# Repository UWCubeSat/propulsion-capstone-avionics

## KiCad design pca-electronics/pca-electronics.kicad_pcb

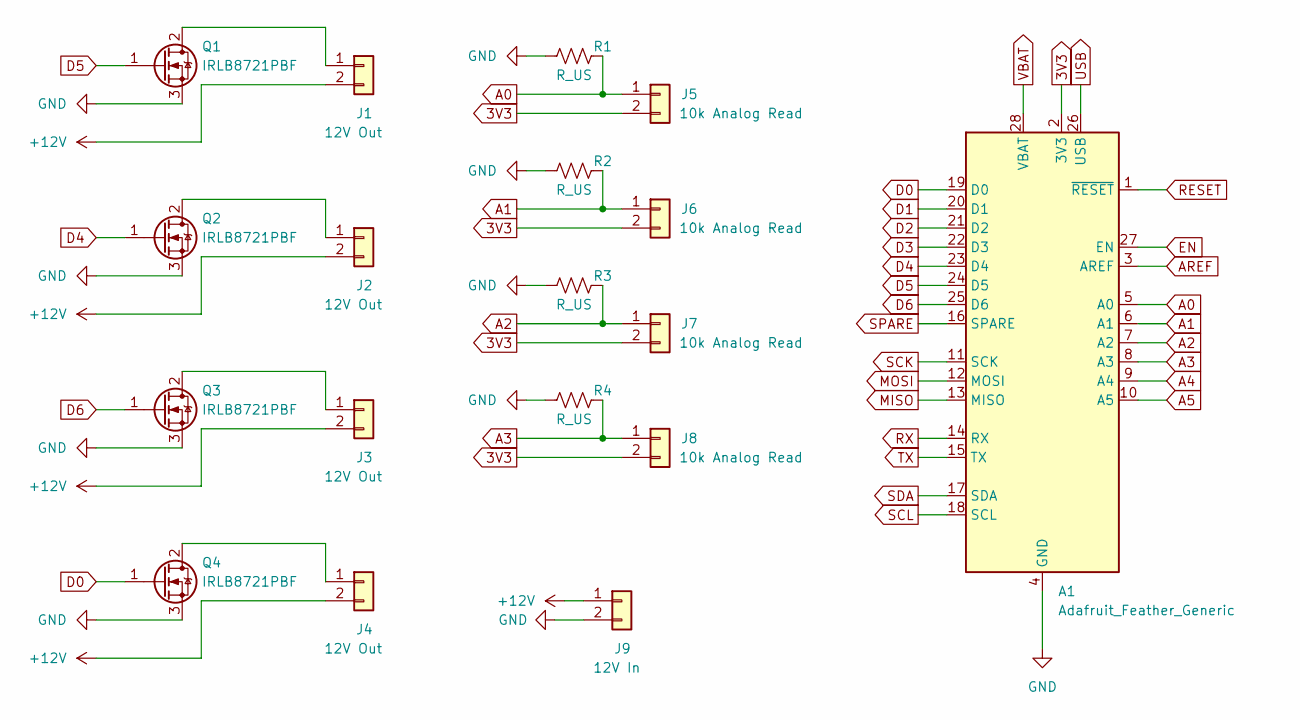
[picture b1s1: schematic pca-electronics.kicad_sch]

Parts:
A1: Adafruit_Feather_Generic; Adafruit_Feather
J1, J2, J3, J4: 12V Out; AMASS_XT30U-M_1x02_P5.0mm_Vertical
J5, J6, J7, J8: 10k Analog Read; JST_PH_B2B-PH-K_1x02_P2.00mm_Vertical
J9: 12V In; AMASS_XT30U-F_1x02_P5.0mm_Vertical
Q1, Q2, Q3, Q4: IRLB8721PBF; TO-220-3_Vertical
R1, R2, R3, R4: R_US; R_Axial_DIN0204_L3.6mm_D1.6mm_P7.62mm_Horizontal

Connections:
3V3: A1.2 (3V3), J5.2, J6.2, J7.2, J8.2
+12V: J1.2, J2.2, J3.2, J4.2, J9.1 (12_V_in)
A0: A1.5 (A0), J5.1, R1.1
A1: A1.6 (A1), J6.1, R2.1
A2: A1.7 (A2), J7.1, R3.1
A3: A1.8 (A3), J8.1, R4.1
A4: A1.9 (A4)
A5: A1.10 (A5)
AREF: A1.3 (AREF)
D0: A1.19 (D0), Q4.1 (G)
D1: A1.20 (D1)
D2: A1.21 (D2)
D3: A1.22 (D3)
D4: A1.23 (D4), Q2.1 (G)
D5: A1.24 (D5), Q1.1 (G)
D6: A1.25 (D6), Q3.1 (G)
EN: A1.27 (EN)
GND: A1.4 (GND), J9.2 (GND), Q1.3 (S), Q2.3 (S), Q3.3 (S), Q4.3 (S), R1.2, R2.2, R3.2, R4.2
MISO: A1.13 (MISO)
MOSI: A1.12 (MOSI)
unnamed: J1.1, Q1.2 (D)
unnamed: J2.1, Q2.2 (D)
unnamed: J3.1, Q3.2 (D)
unnamed: J4.1, Q4.2 (D)
RESET: A1.1 (~RESET)
RX: A1.14 (RX)
SCK: A1.11 (SCK)
SCL: A1.18 (SCL)
SDA: A1.17 (SDA)
SPARE: A1.16 (SPARE)
TX: A1.15 (TX)
USB: A1.26 (USB)
VBAT: A1.28 (VBAT)

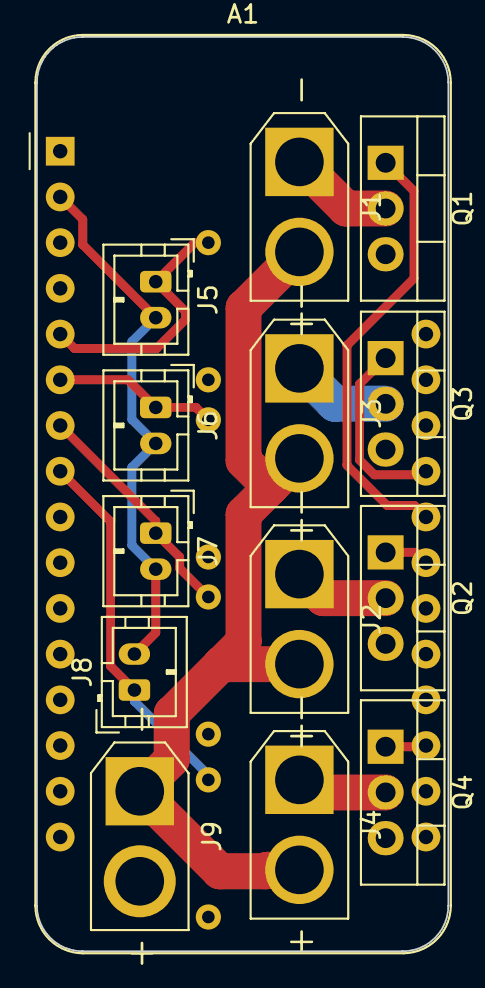
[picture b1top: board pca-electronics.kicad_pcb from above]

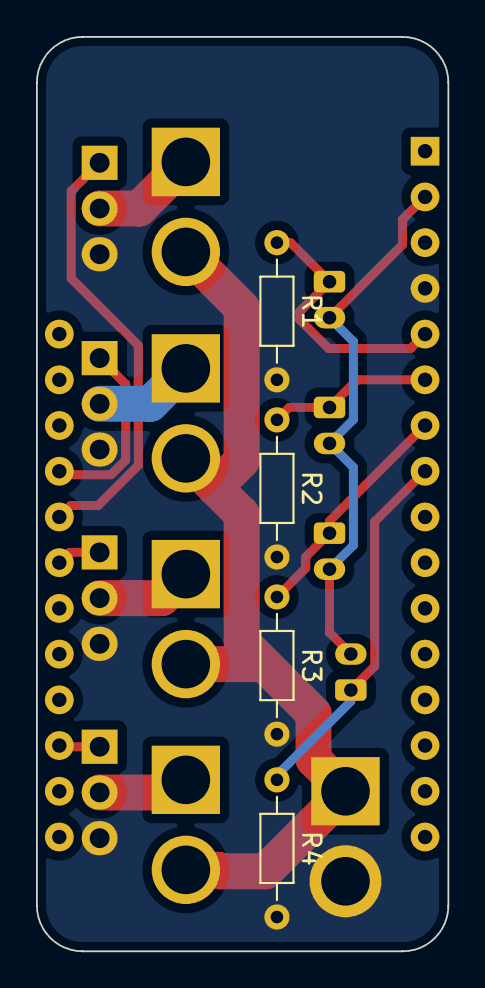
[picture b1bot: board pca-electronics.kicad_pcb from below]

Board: 2 copper layers, 22.9 x 50.8 mm, 18 parts (4 on the bottom side), 15 nets.

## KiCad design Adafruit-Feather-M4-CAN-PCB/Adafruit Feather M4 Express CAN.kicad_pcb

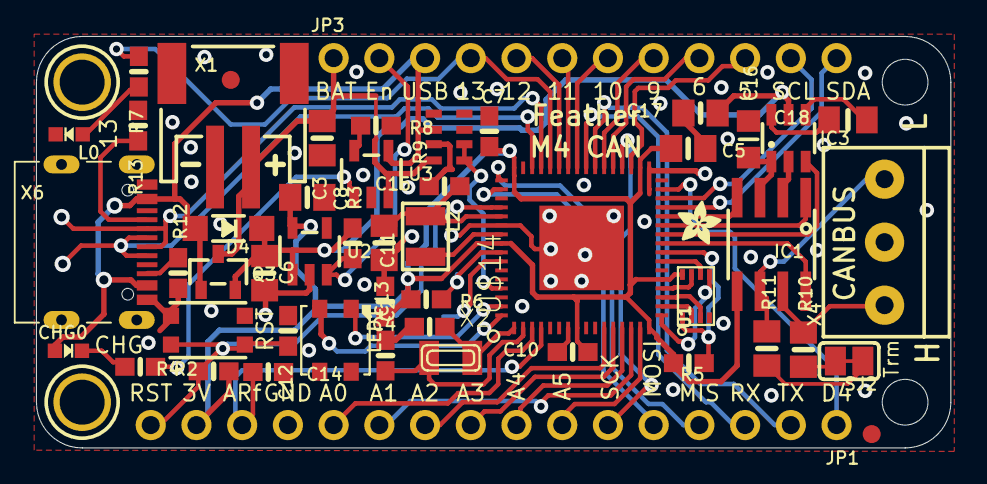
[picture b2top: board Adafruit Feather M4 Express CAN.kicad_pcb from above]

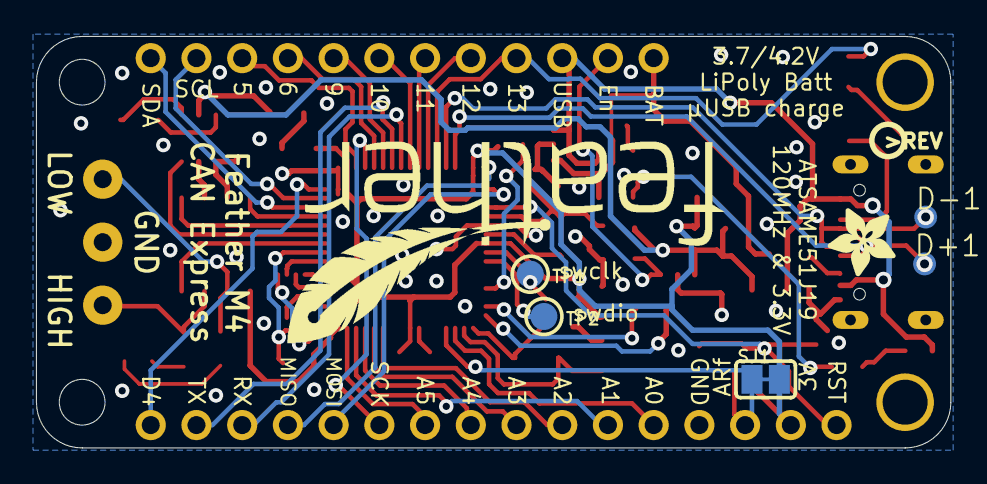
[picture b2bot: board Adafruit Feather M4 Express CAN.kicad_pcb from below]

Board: 2 copper layers, 50.8 x 22.9 mm, 63 parts (8 on the bottom side), 63 nets.

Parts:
@HOLE0, @HOLE1: (no value)
C2, C4: 22pF; 0603-NO
C3, C6, C8: 10µF; 0805-NO
C5, C13, C17: 10uF; 0805-NO
C7, C10, C11, C12, C14, C15: 1uF; 0603-NO
C16: 10uF; _0805MP
C18: 1uF; 0805_10MGAP
CHG0: ORANGE; CHIPLED_0603_NOOUTLINE
D4: MBR540; SOD-123
D+1: TPB1,27; B1,27
D-1: TPB1,27; B1,27
IC1: TCAN1051HGV; SOIC8_150MIL
IC3: AP3602; SOT23-6
JP1: 1X16_ROUND
JP3: 1X12_ROUND
L0: RED; CHIPLED_0603_NOOUTLINE
L2: 10uH; INDUCTOR_1007
LED1: WS2812B3535; LED3535
Q3: DMG341; SOT23-R
R2, R3, R4, R5, R6, R7: 10K; 0603-NO
R8, R12, R13: 5.1K; 0603-NO
R9: 100K; RESPACK_4X0603_NO
R10, R11: 60 ohm; 0805-NO
SJ1, SJ2: SOLDERJUMPER_CLOSEDWIRE
SW1: KMR2; BTN_KMR2_4.6X2.8
TP1, TP2: TESTPOINT_ROUND_1.5MM
U1: 2MB Flash; USON8
U2: AP2112-3.3; SOT23-5@1
U3: MCP73831T-2ACI/OT; SOT23-5
U$1: ADAFRUIT_2.5MM
U$9: FEATHERLOGO
U$12: ADAFRUIT_3.5MM
U$13: PCBFEAT-REV-040
U$14: ATSAMD51J; PQFN64-1
U$31, U$32: MOUNTINGHOLE2.5; MOUNTINGHOLE_2.5_PLATED
U$34, U$35: FIDUCIAL_1MM
X1: JSTPH; JSTPH2_BATT
X2: 32.768; XTAL3215
X4: 3.5mm; TERMBLOCK_1X3-3.5MM
X6: USB Type C; USB_C_CUSB31-CFM2AX-01-X

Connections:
5.0V: C16.1, IC1.3, IC3.1
+3V3: C5.1, C7.1, C8.1, C10.1, C11.1, IC1.5, JP1.15, R4.1, R5.2, R6.1, SJ1.2, U1.8, U2.5, U$14.8, U$14.16, U$14.21, U$14.34, U$14.48, U$14.56
A0: JP1.12, U$14.3
A1: JP1.11, U$14.14
A2: JP1.10, U$14.11
A3: JP1.9, U$14.12
A4: JP1.8, U$14.13
A5: JP1.7, U$14.15
AREF: C14.1, JP1.14, SJ1.1, U$14.4
BOOST_EN: IC3.3, U$14.26
CAN1_RX: IC1.4, U$14.28
CAN1_S: IC1.8, U$14.25
CAN1_TX: IC1.1, U$14.27
CAN_H: IC1.7, R10.2, X4.3
CAN_L: IC1.6, R11.2, X4.1
CC1: R13.2, X6.A5
CC2: R12.2, X6.B5
D4: JP1.1, U$14.31
D5: JP3.10, U$14.35
D6: JP3.9, U$14.37
D8_NEOPIX: LED1.1, U$14.63
D9: JP3.8, U$14.38
D10: JP3.7, U$14.41
D11: JP3.6, U$14.42
D12: JP3.5, U$14.43
D13: JP3.4, R7.1, U$14.44
D+: D+1.TP, U$14.46, X6.A6, X6.B6
D-: D-1.TP, U$14.45, X6.A7, X6.B7
EN: JP3.2, R3.1, U2.3
GND: C2.2, C3.2, C4.2, C5.2, C6.2, C7.2, C8.2, C10.2, C11.2, C12.1, C13.2, C14.2, C15.2, C16.2, C17.2, IC1.2, IC3.2, JP1.13, L0.C, LED1.4, R8.2, R9.3, R9.7, R12.1, R13.1, SW1.B, SW1.B', U1.4, U2.2, U3.2, U$14.7, U$14.22, U$14.33, U$14.47, U$14.54, U$14.EXP, X1.1, X4.2, X6.A1B12, X6.B1A12
MISO: JP1.4, U$14.49
MOSI: JP1.5, U$14.50
unnamed: CHG0.C, R2.1
unnamed: L0.A, R7.2
unnamed: R2.2, U3.1
unnamed: R8.1, U3.5
unnamed: R10.1, SJ2.2
unnamed: C4.1, U$14.1, X2.P$2
unnamed: C18.2, IC3.6
unnamed: C18.1, IC3.4
unnamed: C2.1, U$14.2, X2.P$1
unnamed: L2.P$2, U$14.55
unnamed: R11.1, SJ2.1
NEO_PWR: LED1.2, U$14.64
QSPI_CS: R5.1, U1.1, U$14.24
QSPI_DATA[0]: U1.5, U$14.17
QSPI_DATA[1]: U1.2, U$14.18
QSPI_DATA[2]: U1.3, U$14.19
QSPI_DATA[3]: U1.7, U$14.20
QSPI_SCK: U1.6, U$14.23
RX_D0: JP1.3, U$14.40
SCK: JP1.6, U$14.36
SCL: JP3.11, U$14.30
SDA: JP3.12, U$14.29
SWCLK: R6.2, TP1.P$1, U$14.57
SWDIO: TP2.P$1, U$14.58
TX_D1: JP1.2, U$14.39
VBAT: C3.1, JP3.1, Q3.3, R9.8, U3.3, X1.2
VBUS: CHG0.A, D4.A, JP3.3, Q3.1, R9.6, U3.4, X6.A4B9, X6.B4A9
VDDCORE1: C13.1, C15.1, L2.P$1, U$14.53
VHI: C6.1, C17.1, D4.C, IC3.5, Q3.2, R3.2, U2.1
V_DIV: R9.1, R9.2, U$14.61
~RESET: C12.2, JP1.16, R4.2, SW1.A, SW1.A', U$14.52

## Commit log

2023-02-09 Initial KiCAD project files
2023-02-09 Import Adafruit-Feather-M4-CAN-PCB
2023-02-10 Rough initial prototype work
2023-02-24 Misc electronics work
2023-02-24 Rough initial skeleton of code structure
2023-02-28 More mocking work
